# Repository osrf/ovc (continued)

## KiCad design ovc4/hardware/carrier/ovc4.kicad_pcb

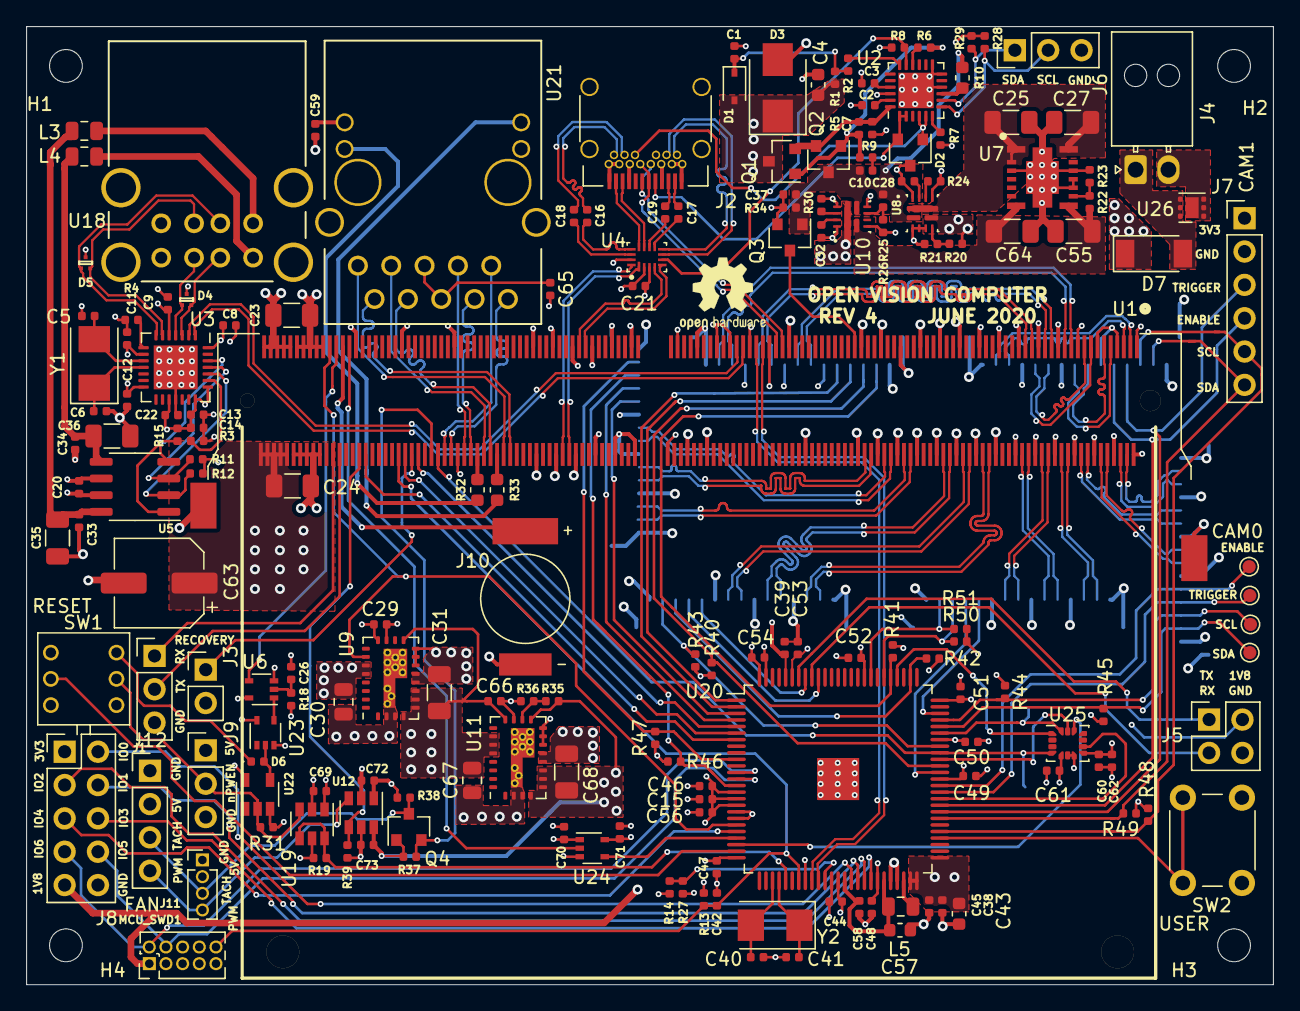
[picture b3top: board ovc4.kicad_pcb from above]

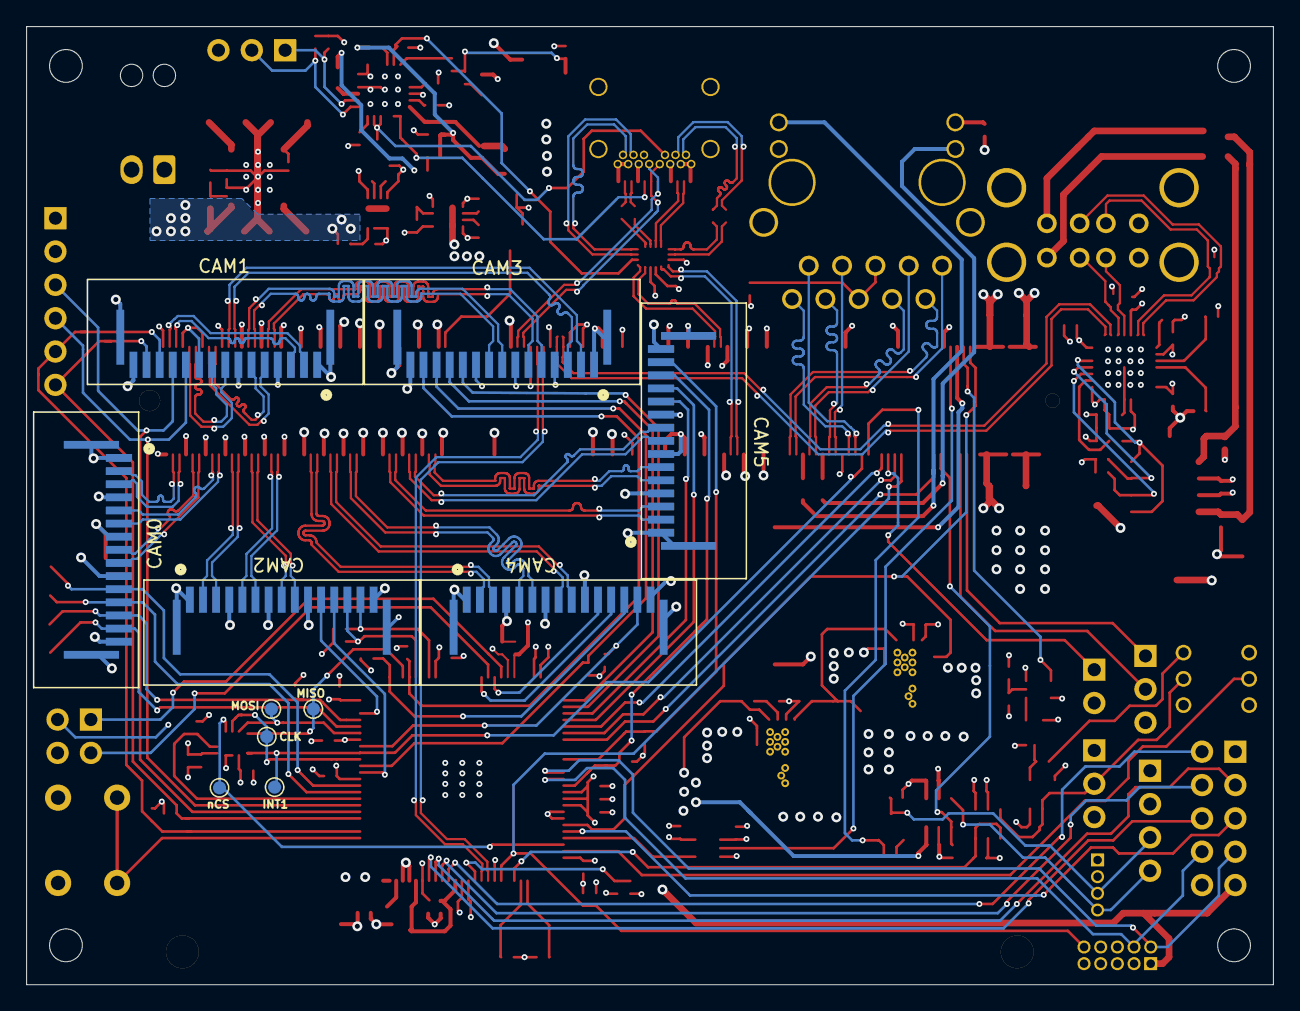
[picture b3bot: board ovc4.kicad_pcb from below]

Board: 6 copper layers, 95.0 x 73.0 mm, 194 parts (11 on the bottom side), 188 nets.

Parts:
C1, C2, C3, C7, C14, C22, C26, C29, C66: 1u; C_0402_1005Metric
C4: 4u7; C_0603_1608Metric
C5, C6, C40, C41: 18p; C_0402_1005Metric
C8: 10u; C_0402_1005Metric
C9, C10, C11, C12, C13, C15, C16, C17, C18, C19, C20, C21, C28, C32, C33, C34, C37, C38, C39, C42, C44, C46, C47, C48, C49, C50, C51, C52, C53, C54, C56, C58, C59, C60, C61, C65, C69, C70, C71, C72, C73: 100n; C_0402_1005Metric
C23, C24, C35, C36: 100u; C_1206_3216Metric
C25, C27: 10u; C_1206_3216Metric
C30, C67: 10u; C_0805_2012Metric
C31, C55, C64, C68: 47u; C_1206_3216Metric
C43, C57: 10u; C_0603_1608Metric
C45: 47p; C_0402_1005Metric
C62: 2u2; C_0402_1005Metric
C63: 470u; CP_Elec_6.3x7.7
CAM0, CAM1, CAM2, CAM3, CAM4, CAM5: PICAM; AMPHENOL_SFW15R
D1: SDMK0340L-7-F; D_SOD-323
D2: ESDA25W; SOT-23
D3: SMBJ22A; D_SMB
D4, D5: D_TVS_x2_AAC; TPD2EUSB30x
D6: D; D_0402_1005Metric
D7: PMEG3030EP,115; D_SOD-128
H1, H2, H3, H4: MountingHole; MountingHole_2.5mm
J1, J6, J9: Conn_01x03; PinHeader_1x03_P2.54mm_Vertical
J2: USB_C_Receptacle; USB_C_Receptacle_Wurth_632723300011
J3: Conn_01x02; PinHeader_1x02_P2.54mm_Vertical
J4: Conn_01x02; Molex_Nano-Fit_105313-xx02_1x02_P2.50mm_Horizontal
J5: ISP_UART; PinHeader_2x02_P2.54mm_Vertical
J7: Conn_01x06; PinHeader_1x06_P2.54mm_Vertical
J8: Conn_02x05_Odd_Even; PinHeader_2x05_P2.54mm_Vertical
J10: Conn_01x02; ELNA_DSK-3R3H224U-HL
J11: Conn_01x04; PinHeader_1x04_P1.27mm_Vertical
J12: Conn_01x04; PinHeader_1x04_P2.54mm_Vertical
L3, L4, L5: 4u7; L_0805_2012Metric
LOGO1: Logo_Open_Hardware_Large; OSHW-Logo2_7.3x6mm_SilkScreen
MCU_SWD1: Conn_ARM_JTAG_SWD_10; PinHeader_2x05_P1.27mm_Vertical
Q1, Q2: SI2369DS; SOT-23
Q3, Q4: 2N7002; SOT-23
R1: 470R; R_0402_1005Metric
R2: 1k; R_0402_1005Metric
R3, R5, R7, R8, R13, R15, R39: 100k; R_0402_1005Metric
R4: 649R; R_0402_1005Metric
R6, R24, R30: 22k; R_0402_1005Metric
R9: 100R; R_0402_1005Metric
R10: 1k; R_0603_1608Metric
R11, R12, R14, R18, R19, R22, R31, R37, R38: 10k; R_0402_1005Metric
R20, R25, R27: 20k; R_0402_1005Metric
R21, R26: 4k7; R_0402_1005Metric
R23, R28, R29, R40, R41, R42, R43, R44, R45, R46, R47, R48, R49, R50, R51: 2k4; R_0402_1005Metric
R32, R33: 110R; R_0603_1608Metric
R34: 1M; R_0402_1005Metric
R35: 340k; R_0402_1005Metric
R36: 162k; R_0402_1005Metric
SW1: SW_DPDT_x2; TL2230
SW2: SW_Push; SW_PUSH_6mm_H5mm
TP1, TP2, TP3, TP4, TP5, TP6, TP7, TP8, TP9: Testpoint; TestPoint_Pad_D1.0mm
U1: Jetson_Nano; TE_2309413-1
U2: STUSB4500; QFN-24-1EP_4x4mm_P0.5mm_EP2.7x2.7mm
U3: CY7C65642-28LTXC; QFN-28-1EP_5x5mm_P0.5mm_EP3.35x3.35mm
U4: HD3SS3202; TI_R_PUQFN_N16
U5: LM3526-L; SO-8_3.9x4.9mm_P1.27mm
U6: 74AHC1G08; SOT-353_SC-70-5
U7: TPSM53604; TI_B3QFN
U8, U10: TPS2121; Texas_VQFN-HR-12_2x2.5_Pitch0.5mm
U9, U11: EN5322QI; Converter_DCDC_Intel_QFN-24_4x6mm_P0.65mm_ThermalVias
U12, U19: SN74LVC1T45DBV; SOT-23-6
U18: USBA_DUAL; USBA_DUAL_HOR
U20: LPC55S69JBD100; QFP-100-1EP_3.21x3.21mm_14x14_Pitch0.5mm
U21: ARJ11C-MBSAS-A-BA-7MU2
U22: 74LVC1G34; SOT-23-5
U23: SN74LVC1G04; SOT-353_SC-70-5
U24: SN74AUP1T34DCK; SOT-353_SC-70-5
U25: ICM42688; LGA-14_3x2.5mm_P0.5mm_LayoutBorder3x4y
U26: TVS2200DRV; WSON-6-1EP_2x2mm_P0.65mm_EP1x1.6mm
Y1: 12MHz; Crystal_SMD_5032-2Pin_5.0x3.2mm
Y2: 16MHz; Crystal_SMD_5032-2Pin_5.0x3.2mm

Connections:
+1V8: C15.2, C38.2, C43.1, C45.2, C46.2, C47.2, C48.2, C49.2, C50.2, C51.2, C52.2, C53.2, C54.2, C56.2, C60.2, C61.2, C62.2, C68.1, C71.1, C73.1, J5.2, J8.9, MCU_SWD1.1 (VTref), Q4.1 (G), R13.2, R35.1, R37.1, R40.1, R41.1, R42.1, R43.1, R44.1, R45.1, R46.1, R47.1, R48.1, R49.1, R50.1, R51.1, U11.4 (VOUT), U11.5 (VOUT), U11.6 (VOUT), U11.7 (VOUT), U11.13 (VSENSE), U12.6 (VCCB), U20.15 (VDD), U20.16 (VDDA), U20.17 (VREFP), U20.25 (VDD), U20.44 (VDD), U20.49 (VBAT_DCDC), U20.50 (VBAT_DCDC), U20.51 (VBAT_PMU), U20.63 (VDD), U20.69 (VDD), U20.75 (VDD), U20.84 (VDD), U20.95 (VDD), U20.100 (VDD), U24.5 (VCCB), U25.5 (VDDIO), U25.8 (VDD)
+3V3: C8.2, C9.2, C11.2, C12.2, C13.2, C14.2, C21.2, C22.2, C31.1, C39.2, C44.2, C59.2, C66.1, C67.1, CAM0.15 (3V3), CAM1.15 (3V3), CAM2.15 (3V3), CAM3.15 (3V3), CAM4.15 (3V3), CAM5.15 (3V3), J7.1, J8.1, R8.1, R11.1, R12.1, R15.1, R28.1, R29.1, U2.22 (VSYS), U3.5 (VCC_A), U3.9 (VCC_A), U3.14 (VCC_A), U3.17 (nRESET), U3.21 (VCC_D), U3.22 (SELFPWR), U3.28 (VREG), U4.3 (VCC), U9.4 (VOUT), U9.5 (VOUT), U9.6 (VOUT), U9.7 (VOUT), U9.13 (VSENSE), U11.10 (VS2), U11.11 (VS1), U11.12 (VS0), U11.16 (AVIN), U11.18 (ENABLE), U11.19 (PVIN), U11.20 (PVIN), U20.38 (USB1_3V3), U20.96 (USB0_3V3), U21.12 (GRNYEL_A), U21.13 (GRN_A)
+5V: C20.2, C23.1, C24.1, C29.1, C30.1, C63.1, C69.1, C70.1, C72.1, J9.1, J11.2, J12.2, R14.1, R18.1, R38.1, U1.251 (VDD_IN), U1.252 (VDD_IN), U1.253 (VDD_IN), U1.254 (VDD_IN), U1.255 (VDD_IN), U1.256 (VDD_IN), U1.257 (VDD_IN), U1.258 (VDD_IN), U1.259 (VDD_IN), U1.260 (VDD_IN), U5.7 (IN), U6.5 (VCC), U9.16 (AVIN), U9.19 (PVIN), U9.20 (PVIN), U10.1 (OUT), U10.8 (OUT), U12.1 (VCCA), U19.1 (VCCA), U22.5 (VCC), U23.5 (VCC), U24.1 (VCCA)
/Interfaces/FAN_PWM: R39.2, U1.230 (GPIO14), U12.4 (B)
/Interfaces/FAN_PWM_5V: J11.4, J12.4, U12.3 (A)
/Interfaces/FAN_TACH: Q4.2 (S), R37.2, U1.208 (GPIO08)
/Interfaces/FAN_TACH_5V: J11.3, J12.3, Q4.3 (D), R38.2
/Interfaces/USB0_VBUS: Q3.3 (D), U1.87 (GPIO0)
/MCU/IMU_CLK: TP2.1, U20.66 (PIO0_28/WAKEUP), U25.13 (SCL/SCLK)
/MCU/IMU_CS: TP1.1, U20.23 (PIO0_31/ADC0_3), U25.12 (CS)
/MCU/IMU_FSYNC: U20.60 (PIO0_26), U25.9 (INT2/FSYNC/CLKIN)
/MCU/IMU_MISO: TP4.1, U20.79 (PIO0_25), U25.1 (SDO/AD0)
/MCU/IMU_MOSI: TP3.1, U20.70 (PIO0_24), U25.14 (SDA/SDIO/SDI)
/MCU/ISP_USART_RXD: J5.3, U20.92 (PIO0_29)
/MCU/ISP_USART_TXD: J5.1, U20.94 (PIO0_30)
/MCU/MCU_GPIO0: J8.2, U20.40 (PIO1_10)
/MCU/MCU_GPIO1: J8.4, U20.41 (PIO1_22)
/MCU/MCU_GPIO2: J8.3, U20.42 (PIO1_23)
/MCU/MCU_GPIO3/FC6: J8.6, U20.43 (PIO1_17)
/MCU/MCU_GPIO4/FC6: J8.5, U20.21 (PIO0_10/ADC0_1)
/MCU/MCU_GPIO_BUTTON: SW2.1, U20.54 (PIO0_0/ACMP0_A)
/MCU/SWDCLK/MCU_GPIO5/FC6: J8.8, MCU_SWD1.4 (SWDCLK/TCK), U20.13 (PIO0_11/ADC0_9)
/MCU/SWDIO/MCU_GPIO6/FC6: J8.7, MCU_SWD1.2 (SWDIO/TMS), U20.12 (PIO0_12/ADC0_10)
/Power/AUX_PWR: D7.2 (A), J4.1, U26.4 (IN), U26.5 (IN), U26.6 (IN)
/Power/BATT: J10.2, U1.235 (PMIC_BBAT)
/Power/CTRL_PWEN: U6.1, U23.4
/Power/MCU_nPWEN_5V: J9.2, R31.1, SW1.2 (B), U19.3 (A), U22.2
/Power/NX_nSHUTDOWN_REQ: U1.233 (nSHUTDOWN_REQ), U24.2 (A)
/Power/OV1: R25.2, R26.1, U10.5 (OV1)
/Power/POWER_EN: U1.237 (POWER_EN), U6.4
/Power/PR1: R20.2, R21.1, U8.6 (PR1)
/Power/VAUX: D7.1 (K), R20.1, U8.7 (IN1)
/Power/VREG_5V: C55.1, C64.1, R22.1, U7.7 (VOUT), U7.8 (VOUT), U10.2 (IN2)
/Power/VREG_IN: C25.1, C27.1, U7.1 (VIN), U7.2 (EN), U7.14 (VIN), U8.1 (OUT), U8.8 (OUT)
/Power/nFORCE_RECOVERY: J3.1, U1.214 (nFORCE_RECOVERY)
/Power/nPWEN_LATCH: D6.2 (A), U22.4, U23.2
/USB/1V2: C3.1, U2.21 (VREG_1V2)
/USB/2V7: C2.1, U2.23 (VREG_2V7)
/USB/ABSIDE: R8.2, U2.17 (A_B_SIDE), U4.6 (SEL)
/USB/CONN_CC1: D2.2 (K), J2.A5 (CC1), U2.1 (CC1DB), U2.2 (CC1)
/USB/CONN_CC2: D2.1 (K), J2.B5 (CC2), U2.4 (CC2), U2.5 (CC2DB)
/USB/CONN_RX1+: J2.B11 (RX1+), U4.8 (C1+)
/USB/CONN_RX1-: J2.B10 (RX1-), U4.7 (C1-)
/USB/CONN_RX2+: J2.A11 (RX2+), U4.12 (B1+)
/USB/CONN_RX2-: J2.A10 (RX2-), U4.11 (B1-)
/USB/CONN_TX1+: C17.2, J2.A2 (TX1+)
/USB/CONN_TX1-: C19.2, J2.A3 (TX1-)
/USB/CONN_TX2+: C16.2, J2.B2 (TX2+)
/USB/CONN_TX2-: C18.2, J2.B3 (TX2-)
/USB/CONN_VBUS: C4.1, D1.2 (A), D3.1 (A1), J2.A4 (VBUS), J2.A9 (VBUS), J2.B4 (VBUS), J2.B9 (VBUS), Q1.3 (D), R1.1
/USB/DISCH: R10.2, U2.9 (DISCH)
/USB/GATES: Q1.1 (G), Q2.1 (G), R5.2, R6.1, R9.2
/USB/HUB_nOVR0: R11.2, U3.25 (nOVR1), U5.3 (FLAGB)
/USB/HUB_nOVR1: R12.2, U3.24 (nOVR2), U5.2 (FLAGA)
/USB/HUB_nPWR: R15.2, U3.26 (nPWR/SDA), U5.1 (nENA), U5.4 (nENB)
/USB/RESET: R7.1, U2.6 (RESET)
/USB/T1+: C17.1, U4.9 (C0-)
/USB/T1-: C19.1, U4.10 (C0+)
/USB/T2+: C16.1, U4.13 (B0-)
/USB/T2-: C18.1, U4.14 (B0+)
/USB/USB0_D_N: J2.A7 (D-), J2.B7 (D-), U1.109 (USB0_D_N)
/USB/USB0_D_P: J2.A6 (D+), J2.B6 (D+), U1.111 (USB0_D_P)
/USB/USB2_D_N: U1.121 (USB2_D_N), U3.1 (D_N)
/USB/USB2_D_P: U1.123 (USB2_D_P), U3.2 (D_P)
/USB/USB2_USER0_D_N: D4.2 (A2), U3.3 (DD1_N), U18.2 (D-A)
/USB/USB2_USER0_D_P: D4.1 (A1), U3.4 (DD1_P), U18.3 (D+A)
/USB/USB2_USER1_D_N: D5.2 (A2), U3.6 (DD2_N), U18.7 (D+B)
/USB/USB2_USER1_D_P: D5.1 (A1), U3.7 (DD2_P), U18.6 (D-B)
/USB/USBSS_RX_N: U1.161 (USBSS_RX_N), U4.5 (A1-)
/USB/USBSS_RX_P: U1.163 (USBSS_RX_P), U4.4 (A1+)
/USB/USBSS_TX_N: U1.168 (USBSS_TX_P), U4.16 (A0+)
/USB/USBSS_TX_P: U1.166 (USBSS_TX_N), U4.1 (A0-)
/USB/VBUS_USER0: L4.2, U18.1 (VBUSA)
/USB/VBUS_USER1: L3.2, U18.5 (VBUSB)
/USB/VCC_USER0USB: C34.2, C36.2, L4.1, U5.5 (OUTB)
/USB/VCC_USER1USB: C33.2, C35.2, L3.1, U5.8 (OUTA)
CAM0_CLK+: CAM0.9 (CLK+), U1.12 (CSI0_CLK_P)
CAM0_CLK-: CAM0.8 (CLK-), U1.10 (CSI0_CLK_N)
CAM0_DAT0+: CAM0.3 (DAT0+), U1.6 (CSI0_D0_P)
CAM0_DAT0-: CAM0.2 (DAT0-), U1.4 (CSI0_D0_N)
CAM0_DAT1+: CAM0.6 (DAT1+), U1.18 (CSI0_D1_P)
CAM0_DAT1-: CAM0.5 (DAT1-), U1.16 (CSI0_D1_N)
CAM0_ENABLE: CAM0.11 (ENABLE), TP9.1, U20.62 (PIO1_3)
CAM0_SCL_1V8: CAM0.13 (SCL), R44.2, TP7.1, U20.72 (PIO0_14)
CAM0_SDA_1V8: CAM0.14 (SDA), R45.2, TP6.1, U20.71 (PIO0_13)
CAM0_TRIGGER: CAM0.12 (GPIO/NC), TP8.1, U20.61 (PIO1_2)
CAM1_CLK+: CAM1.9 (CLK+), U1.11 (CSI1_CLK_P)
CAM1_CLK-: CAM1.8 (CLK-), U1.9 (CSI1_CLK_N)
CAM1_DAT0+: CAM1.3 (DAT0+), U1.5 (CSI1_D0_P)
CAM1_DAT0-: CAM1.2 (DAT0-), U1.3 (CSI1_D0_N)
CAM1_DAT1+: CAM1.6 (DAT1+), U1.17 (CSI1_D1_P)
CAM1_DAT1-: CAM1.5 (DAT1-), U1.15 (CSI1_D1_N)
CAM1_ENABLE: CAM1.11 (ENABLE), J7.4, U20.59 (PIO1_1/WAKEUP)
CAM1_SCL_1V8: CAM1.13 (SCL), J7.5, R48.2, U20.55 (PIO0_9/ACMP0_B)
CAM1_SDA_1V8: CAM1.14 (SDA), J7.6, R49.2, U20.57 (PIO1_14/ACMP0_D)
CAM1_TRIGGER: CAM1.12 (GPIO/NC), J7.3, U20.58 (PIO1_19/ACMPVREF)
CAM2_CLK+: CAM2.9 (CLK+), U1.30 (CSI2_CLK_P)
CAM2_CLK-: CAM2.8 (CLK-), U1.28 (CSI2_CLK_N)
CAM2_DAT0+: CAM2.3 (DAT0+), U1.24 (CSI2_D0_P)
CAM2_DAT0-: CAM2.2 (DAT0-), U1.22 (CSI2_D0_N)
CAM2_DAT1+: CAM2.6 (DAT1+), U1.36 (CSI2_D1_P)
CAM2_DAT1-: CAM2.5 (DAT1-), U1.34 (CSI2_D1_N)
CAM2_ENABLE: CAM2.11 (ENABLE), U20.73 (PIO1_28)
CAM2_SCL_1V8: CAM2.13 (SCL), R50.2, U20.81 (PIO0_2/TRST)
CAM2_SDA_1V8: CAM2.14 (SDA), R51.2, U20.83 (PIO0_3/TCK)
CAM2_TRIGGER: CAM2.12 (GPIO/NC), U20.64 (PIO1_18/WAKEUP)
CAM3_CLK+: CAM3.9 (CLK+), U1.29 (CSI3_CLK_P)
CAM3_CLK-: CAM3.8 (CLK-), U1.27 (CSI3_CLK_N)
CAM3_DAT0+: CAM3.3 (DAT0+), U1.23 (CSI3_D0_P)
CAM3_DAT0-: CAM3.2 (DAT0-), U1.21 (CSI3_D0_N)
CAM3_DAT1+: CAM3.6 (DAT1+), U1.35 (CSI3_D1_P)
CAM3_DAT1-: CAM3.5 (DAT1-), U1.33 (CSI3_D1_N)
CAM3_ENABLE: CAM3.11 (ENABLE), U20.2 (PIO1_13)
CAM3_SCL_1V8: CAM3.13 (SCL), R40.2, U20.65 (PIO1_30/WAKEUP)
CAM3_SDA_1V8: CAM3.14 (SDA), R41.2, U20.80 (PIO1_29)
CAM3_TRIGGER: CAM3.12 (GPIO/NC), U20.1 (PIO1_4)
CAM4_CLK+: CAM4.9 (CLK+), U1.54 (CSI4_CLK_P)
CAM4_CLK-: CAM4.8 (CLK-), U1.52 (CSI4_CLK_N)
CAM4_DAT0+: CAM4.3 (DAT0+), U1.48 (CSI4_D0_P)
CAM4_DAT0-: CAM4.2 (DAT0-), U1.46 (CSI4_D0_N)
CAM4_DAT1+: CAM4.6 (DAT1+), U1.60 (CSI4_D1_P)
CAM4_DAT1-: CAM4.5 (DAT1-), U1.58 (CSI4_D1_N)
CAM4_ENABLE: CAM4.11 (ENABLE), U20.93 (PIO1_11)
CAM4_SCL_1V8: CAM4.13 (SCL), R42.2, U20.77 (PIO1_25)
CAM4_SDA_1V8: CAM4.14 (SDA), R43.2, U20.68 (PIO1_26)
CAM4_TRIGGER: CAM4.12 (GPIO/NC), U20.91 (PIO1_31)
CAM5_CLK+: CAM5.9 (CLK+), U1.78 (DSI_CLK_P)
CAM5_CLK-: CAM5.8 (CLK-), U1.76 (DSI_CLK_N)
CAM5_DAT0+: CAM5.3 (DAT0+), U1.72 (DSI_D0_P)
CAM5_DAT0-: CAM5.2 (DAT0-), U1.70 (DSI_D0_N)
CAM5_DAT1+: CAM5.6 (DAT1+), U1.84 (DSI_D1_P)
CAM5_DAT1-: CAM5.5 (DAT1-), U1.82 (DSI_D1_N)
CAM5_ENABLE: CAM5.11 (ENABLE), U20.3 (PIO1_24)
CAM5_SCL_1V8: CAM5.13 (SCL), R46.2, U20.14 (PIO0_16/ADC0_8)
CAM5_SDA_1V8: CAM5.14 (SDA), R47.2, U20.10 (PIO1_9/ADC0_12)
CAM5_TRIGGER: CAM5.12 (GPIO/NC), U20.4 (PIO1_20)
DEBUG_UART_RXD: J1.1, U1.238 (UART2_RXD)
DEBUG_UART_TXD: J1.2, U1.236 (UART2_TXD)
FRAME_TRIGGER: U1.212 (GPIO10), U20.5 (PIO1_6)
GBE_LED_ACT: R32.2, U1.194 (GBE_LED_ACT)
GBE_LED_LINK: R33.2, U1.188 (GBE_LED_LINK)
GBE_MDI0_N: U1.184 (GBE_MDI0_N), U21.2 (TRD0-)
GBE_MDI0_P: U1.186 (GBE_MDI0_P), U21.1 (TRD0+)
GBE_MDI1_N: U1.190 (GBE_MDI1_N), U21.4 (TRD1-)
GBE_MDI1_P: U1.192 (GBE_MDI1_P), U21.3 (TRD1+)
GBE_MDI2_N: U1.196 (GBE_MDI2_N), U21.8 (TRD2-)
GBE_MDI2_P: U1.198 (GBE_MDI2_P), U21.7 (TRD2+)
GBE_MDI3_N: U1.202 (GBE_MDI3_N), U21.10 (TRD3-)
GBE_MDI3_P: U1.204 (GBE_MDI3_P), U21.9 (TRD3+)
GND: C1.2, C2.2, C3.2, C4.2, C5.1, C6.2, C7.2, C8.1, C9.1, C11.1, C12.1, C13.1, C14.1, C15.1, C20.1, C21.1, C22.1, C23.2, C24.2, C25.2, C26.2, C27.2, C28.2, C29.2, C30.2, C31.2, C32.2, C33.1, C34.1, C35.1, C36.1, C37.2, C38.1, C39.1, C40.1, C41.1, C42.2, C43.2, C44.1, C45.1, C46.1, C47.1, C48.1, C49.1, C50.1, C51.1, C52.1, C53.1, C54.1, C55.2, C56.1, C57.2, C58.1, C59.1, C60.1, C61.1, C62.1, C63.2, C64.2, C65.2, C66.2, C67.2, C68.2, C69.2, C70.2, C71.2, C72.2, C73.2, CAM0.1 (GND), CAM0.4 (GND), CAM0.7 (GND), CAM0.10 (GND), CAM0.16 (PAD), CAM1.1 (GND), CAM1.4 (GND), CAM1.7 (GND), CAM1.10 (GND), CAM1.16 (PAD), CAM2.1 (GND), CAM2.4 (GND), CAM2.7 (GND), CAM2.10 (GND), CAM2.16 (PAD), CAM3.1 (GND), CAM3.4 (GND), CAM3.7 (GND), CAM3.10 (GND), CAM3.16 (PAD), CAM4.1 (GND), CAM4.4 (GND), CAM4.7 (GND), CAM4.10 (GND), CAM4.16 (PAD), CAM5.1 (GND), CAM5.4 (GND), CAM5.7 (GND), CAM5.10 (GND), CAM5.16 (PAD), D2.3 (A), D3.2 (A2), D4.3 (common), D5.3 (common), J1.3, J2.A1 (GND), J2.A12 (GND), J2.B1 (GND), J2.B12 (GND), J2.S1 (SHIELD), J3.2, J4.2, J5.4, J6.3, J7.2, J8.10, J9.3, J10.1, J11.1, J12.1, MCU_SWD1.3 (GND), MCU_SWD1.5 (GND), MCU_SWD1.9 (GNDDetect), Q3.2 (S), R3.2, R4.2, R7.2, R19.1, R21.2, R23.2, R24.2, R26.2, R27.2, R30.2, R31.2, R34.2, R36.2, R39.1, SW1.6 (C), SW2.2, U1.1 (GND), U1.2 (GND), U1.7 (GND), U1.8 (GND), U1.13 (GND), U1.14 (GND), U1.19 (GND), U1.20 (GND), U1.25 (GND), U1.26 (GND), U1.31 (GND), U1.32 (GND), U1.37 (GND), U1.38 (GND), U1.43 (GND), U1.44 (GND), U1.49 (GND), U1.50 (GND), U1.55 (GND), U1.56 (GND), U1.61 (GND), U1.62 (GND), U1.67 (GND), U1.68 (GND), U1.73 (GND), U1.74 (GND), U1.79 (GND), U1.80 (GND), U1.85 (GND), U1.86 (GND), U1.102 (GND), U1.107 (GND), U1.113 (GND), U1.119 (GND), U1.125 (GND), U1.129 (GND), U1.132 (GND), U1.135 (GND), U1.138 (GND), U1.141 (GND), U1.144 (GND), U1.146 (GND), U1.147 (GND), U1.152 (GND), U1.153 (GND), U1.158 (GND), U1.159 (GND), U1.164 (GND), U1.165 (GND), U1.170 (GND), U1.171 (GND), U1.176 (GND), U1.177 (GND), U1.200 (GND), U1.201 (GND), U1.217 (GND), U1.231 (GND), U1.241 (GND), U1.242 (GND), U1.243 (GND), U1.244 (GND), U1.245 (GND), U1.246 (GND), U1.247 (GND), U1.248 (GND), U1.249 (GND), U1.250 (GND), U1.261 (MNT), U1.262 (MNT), U2.10 (GND), U2.12 (ADDR0), U2.13 (ADDR1), U2.25 (PAD), U3.18 (TEST/SCL), U3.29 (GND), U4.2 (GND), U4.15 (~OE), U5.6 (GND), U6.3 (GND), U7.3 (NC/GND), U7.10 (NC/GND), U7.11 (NC/GND), U7.12 (AGND), U7.15 (PGND), U8.3 (CP2), U8.4 (OV2), U8.5 (OV1), U8.9 (ST), U8.12 (GND), U9.2 (PGND), U9.3 (PGND), U9.8 (PGND), U9.9 (PGND), U9.10 (VS2), U9.11 (VS1), U9.12 (VS0), U9.15 (AGND), U9.25 (PGND), U10.3 (CP2), U10.6 (PR1), U10.9 (ST), U10.12 (GND), U11.2 (PGND), U11.3 (PGND), U11.8 (PGND), U11.9 (PGND), U11.15 (AGND), U11.25 (PGND), U12.2 (GND), U12.5 (DIR), U18.4 (GNDA), U18.8 (GNDB), U18.9 (Shield), U19.2 (GND), U19.5 (DIR), U20.18 (VREFN), U20.19 (VSSA), U20.33 (USB1_VSS), U20.37 (USB1_VSS), U20.46 (VSS_DCDC), U20.47 (VSS_DCDC), U20.99 (USB0_VSS), U20.101 (VSS), U21.MNT, U21.SHLD, U22.3 (GND), U23.3 (GND), U24.3 (GND), U25.6 (GND), U25.7 (RESV/GND), U26.1 (GND), U26.2 (GND), U26.3 (GND), U26.7 (GND)
IMU_INT1: TP5.1, U1.206 (GPIO07), U20.67 (PIO1_12), U25.4 (INT1/INT)
MCU_USB1_D_N: U1.115 (USB1_D_N), U20.35 (USB1_DM)
MCU_USB1_D_P: U1.117 (USB1_D_P), U20.34 (USB1_DP)
MCU_nPWEN: R19.2, U19.4 (B), U19.6 (VCCB), U20.30 (PIO1_21)
NX_MCU_BOOT: U1.228 (GPIO13), U20.7 (PIO0_1)
NX_MCU_GPIO: U1.216 (GPIO11), U20.6 (PIO0_7)
NX_MCU_nRST: C42.1, MCU_SWD1.10 (~RESET~), R13.1, U1.218 (GPIO12), U20.32 (RESETN)
unnamed: C1.1, D1.1 (K), R1.2, R2.1
unnamed: C5.2, U3.10 (XIN), Y1.2
unnamed: C6.1, U3.11 (XOUT), Y1.1
unnamed: C7.1, Q1.2 (S), Q2.2 (S), R5.1, U2.24 (VDD)
unnamed: C10.2, R9.1
unnamed: C26.1, R18.2, U6.2
unnamed: C28.1, U8.11 (SS)
unnamed: C32.1, U10.11 (SS)
unnamed: C40.2, U20.28 (XTAL32M_N), Y2.2
unnamed: C41.2, U20.29 (XTAL32M_P), Y2.1
unnamed: C57.1, C58.2, L5.2, U20.39 (VDD_PMU), U20.45 (FB)
unnamed: C65.1, U21.5 (CT), U21.6 (CT)
unnamed: D6.1 (K), SW1.1 (A)
unnamed: L5.1, U20.48 (LX)
unnamed: R2.2, U2.18 (VBUS_VS_DISCH)
unnamed: R3.1, U3.23 (GANG)
unnamed: R4.1, U3.8 (RREF)
unnamed: R6.2, U2.16 (VBUS_EN_SINK)
unnamed: R14.2, R27.1, U20.36 (USB1_VBUS)
unnamed: R22.2, R23.1, U7.9 (FB)
unnamed: R24.1, U8.10 (ILIM)
unnamed: R30.1, U10.10 (ILIM)
unnamed: R32.1, U21.11 (GRNYEL_C)
unnamed: R33.1, U21.14 (GRN_C)
unnamed: R35.2, R36.1, U11.14 (VFB)
RST_BUTTON: SW1.5 (B), U20.24 (PIO1_8/ADC0_4)
USB_SCL: J6.2, R28.2, U2.7 (SCL)
USB_SDA: J6.1, R29.2, U2.8 (SDA)
VBUS: C10.1, C37.1, Q2.3 (D), Q3.1 (G), R10.1, R25.1, R34.1, U8.2 (IN2), U10.7 (IN1)
nSHUTDOWN_REQ: U20.22 (PIO0_15/ADC0_2), U24.4 (B)
nSYS_RESET: U1.239 (nSYS_RESET), U9.18 (ENABLE), U20.20 (PIO0_23)

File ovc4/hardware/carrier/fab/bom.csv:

Component,Quantity Per PCB,References,Value,Footprint,MFN,MPN,D1N,D1PN,voltage
1,41,C9 C10 C11 C12 C13 C15 C16 C17 C18 C19 C20 C21 C28 C32 C33 C34 C37 C38 C39 C42 C44 C46 C47 C48 C49 C50 C51 C52 C53 C54 C56 C58 C59 C60 C61 C65 C69 C70 C71 C72 C73,100n,C_0402_1005Metric,Samsung,CL05F104ZO5NNNC,Digikey,1276-1004-1-ND,
2,4,C23 C24 C35 C36,100u,C_1206_3216Metric,TDK,C3216X5R1A107M160AC,Digikey,445-6007-1-ND,
3,2,C25 C27,10u,C_1206_3216Metric,KEMET,C1206C106M3PACTU,Digikey,399-8153-1-ND,
4,2,C30 C67,10u,C_0805_2012Metric,Kemet,C0805C106K8PACTU,Digikey,399-4925-1-ND,
5,2,C43 C57,10u,C_0603_1608Metric,Murata,GRM188R61A106KE69J,Digikey,490-14372-1-ND,
6,1,C8,10u,C_0402_1005Metric,Murata,GRM155C80J106ME11J,Digikey,490-18210-1-ND,
7,4,C5 C6 C40 C41,18p,C_0402_1005Metric,Yageo,CC0402JRNPO9BN180,Digikey,311-1415-1-ND,
8,9,C1 C2 C3 C7 C14 C22 C26 C29 C66,1u,C_0402_1005Metric,Samsung,CL05A105KA5NQNC,Digikey,1276-1445-1-ND,
9,1,C62,2u2,C_0402_1005Metric,Murata,GRM155R61A225KE95D,Digikey,490-10451-1-ND,
10,1,C63,470u,CP_Elec_6.3x7.7,Panasonic,EEE-FTJ471XAP,Digikey,P15096CT-ND,
11,1,C45,47p,C_0402_1005Metric,Kemet,C0402C470K5GACTU,Digikey,399-7796-1-ND,
12,4,C31 C55 C64 C68,47u,C_1206_3216Metric,Murata,GRM31CR61A476KE15L,Digikey,490-9673-1-ND,
13,1,C4,4u7,C_0603_1608Metric,Samsung,CL10A475KA8NQNC,Digikey,1276-1900-1-ND,25V
14,6,CAM0 CAM1 CAM2 CAM3 CAM4 CAM5,PICAM,AMPHENOL_SFW15R,Amphenol,SFW15R-1STE1LF,Digikey,609-1905-1-ND,
15,1,D6,D,D_0402_1005Metric,Comchip,CDBQR0130L,Digikey,641-1271-1-ND,
16,2,D4 D5,D_TVS_x2_AAC,TPD2EUSB30x,TI,TPD2EUSB30DRTR,Digikey,296-25509-1-ND,
17,1,D2,ESDA25W,SOT-23,ST,ESDA25W,Digikey,497-6689-1-ND,
18,1,D7,"PMEG3030EP,115",D_SOD-128,Nexperia,"PMEG3030EP,115",Digikey,1727-5324-1-ND,
19,1,D1,SDMK0340L-7-F,D_SOD-323,Diodes Inc,SDMK0340L-7-F,Digikey,SDMK0340L-FDICT-ND,
20,1,D3,SMBJ22A,D_SMB,Bourns,SMBJ22A,Digikey,SMBJ22ABCT-ND,
21,1,J10,Conn_01x02,ELNA_DSK-3R3H224U-HL,Elna,DSK-3R3H224U-HL,Digikey,604-1020-1-ND,
22,1,J3,Conn_01x02,PinHeader_1x02_P2.54mm_Vertical,Harwin,952-2262-ND,Digikey,952-2262-ND,
23,1,J4,Conn_01x02,Molex_Nano-Fit_105313-xx02_1x02_P2.50mm_Horizontal,Molex,1053131302,Digikey,WM15141-ND,
24,3,J1 J6 J9,Conn_01x03,PinHeader_1x03_P2.54mm_Vertical,Wurth,CONN HEADER VERT 3POS 2.54MM,Digikey,732-5316-ND,
25,1,J11,Conn_01x04,PinHeader_1x04_P1.27mm_Vertical,Adam Tech,HPH1-B-04-UA,Digikey,2057-HPH1-B-04-UA-ND,
26,1,J12,Conn_01x04,PinHeader_1x04_P2.54mm_Vertical,Wurth,61300411121,Digikey,732-5317-ND,
27,1,J7,Conn_01x06,PinHeader_1x06_P2.54mm_Vertical,Amphenol,68000-406HLF,Digikey,609-3263-ND,
28,1,J8,Conn_02x05_Odd_Even,PinHeader_2x05_P2.54mm_Vertical,Sullins,PPTC052LFBN-RC,Digikey,S6105-ND,
29,1,J5,ISP_UART,PinHeader_2x02_P2.54mm_Vertical,Harwin,M20-9760246,Digikey,952-1772-ND,
30,1,J2,USB_C_Receptacle,USB_C_Receptacle_Wurth_632723300011,Wurth,632723300011,Digikey,732-9618-1-ND,
31,3,L3 L4 L5,4u7,L_0805_2012Metric,Murata,LQM2MPN4R7MG0L,Digikey,490-12073-1-ND,
32,1,LOGO1,Logo_Open_Hardware_Large,OSHW-Logo2_7.3x6mm_SilkScreen,,,,,
33,1,MCU_SWD1,Conn_ARM_JTAG_SWD_10,PinHeader_2x05_P1.27mm_Vertical,Amphenol,20021111-00010T4LF,Digikey,609-3712-ND,
34,2,Q3 Q4,2N7002,SOT-23,Nexperia,"2N7002,215",Digikey,1727-2764-1-ND,
35,2,Q1 Q2,SI2369DS,SOT-23,Vishay,SI2369DS-T1-GE3,Digikey,SI2369DS-T1-GE3CT-ND,
36,1,R9,100R,R_0402_1005Metric,Panasonic,ERA-2AED101X,Digikey,P100DECT-ND,
37,7,R3 R5 R7 R8 R13 R15 R39,100k,R_0402_1005Metric,Panasonic,ERA-2AED104X,Digikey,P100KDECT-ND,
38,9,R11 R12 R14 R18 R19 R22 R31 R37 R38,10k,R_0402_1005Metric,Panasonic,ERA-2AED103X,Digikey,P10KDECT-ND,
39,2,R32 R33,110R,R_0603_1608Metric,Panasonic,ERA-3AEB111V,Digikey,P110DBCT-ND,
40,1,R36,162k,R_0402_1005Metric,Panasonic,ERJ-2RKF1623X,Digikey,P162KLCT-ND,
41,1,R34,1M,R_0402_1005Metric,Yageo,RC0402FR-071ML,Digikey,311-1.00MLRCT-ND,
42,1,R10,1k,R_0603_1608Metric,Rohm,ESR03EZPJ102,Digikey,RHM1.0KDCT-ND,
43,1,R2,1k,R_0402_1005Metric,Panasonic,ERJ-2RKF1001X,Digikey,P1.00KLCT-ND,
44,3,R20 R25 R27,20k,R_0402_1005Metric,Panasonic,ERA-2AED203X,Digikey,P20KDECT-ND,
45,3,R6 R24 R30,22k,R_0402_1005Metric,Panasonic,ERJ-2RKF2202X,Digikey,P22.0KLCT-ND,
46,15,R23 R28 R29 R40 R41 R42 R43 R44 R45 R46 R47 R48 R49 R50 R51,2k4,R_0402_1005Metric,Panasonic,ERA-2AED242X,Digikey,P2.4KDECT-ND,
47,1,R35,340k,R_0402_1005Metric,Panasonic,ERJ-2RKF3403X,Digikey,P340KLCT-ND,
48,1,R1,470R,R_0402_1005Metric,Panasonic,ERJ-2RKF4700X,Digikey,P470LCT-ND,
49,2,R21 R26,4k7,R_0402_1005Metric,Panasonic,ERJ-2RKF4701X,Digikey,P4.70KLCT-ND,
50,1,R4,649R,R_0402_1005Metric,Panasonic,ERA-2AEB6490X,Digikey,P649DCCT-ND,
51,1,SW1,SW_DPDT_x2,TL2230,E-Switch,TL2230OAF140,Digikey,EG6032-ND,
52,1,SW2,SW_Push,SW_PUSH_6mm_H5mm,TE Connectivity,1825910-7,Digikey,450-1804-ND,
53,1,U6,74AHC1G08,SOT-353_SC-70-5,TI,SN74AHC1G08DCKR,Digikey,296-8743-1-ND,
54,1,U22,74LVC1G34,SOT-23-5,TI,SN74LVC1G34DBVR,Digikey,296-17893-1-ND,
55,1,U21,ARJ11C-MBSAS-A-BA-7MU2,ARJ11C-MBSAS-A-BA-7MU2,Abracon,ARJ11C-MBSAS-A-BA-7MU2,Digikey,ARJ11C-MBSAS-A-BA-7MU2-ND,
56,1,U3,CY7C65642-28LTXC,QFN-28-1EP_5x5mm_P0.5mm_EP3.35x3.35mm,Cypress,CY7C65642-28LTXC,Digikey,428-3149-ND,
57,2,U9 U11,EN5322QI,Converter_DCDC_Intel_QFN-24_4x6mm_P0.65mm_ThermalVias,Intel,EN5322QI,Digikey,544-2849-1-ND,
58,1,U4,HD3SS3202,TI_R_PUQFN_N16,TI,HD3SS3202IRSVT,Digikey,296-52295-1-ND,
59,1,U25,ICM42688,LGA-14_3x2.5mm_P0.5mm_LayoutBorder3x4y,TDK Invensense,ICM-42688-P,Digikey,1428-ICM-42688-PCT-ND,
60,1,U1,Jetson_Nano,TE_2309413-1,TE Connectivity,2309413-1,Digikey,A126764CT-ND,
61,1,U5,LM3526-L,SO-8_3.9x4.9mm_P1.27mm,TI,LM3526MX-L/NOPB,Digikey,LM3526MX-L/NOPBCT-ND,
62,1,U20,LPC55S66JBD100,QFP-100-1EP_3.21x3.21mm_14x14_Pitch0.5mm,NXP,LPC55S69JBD100K,Digikey,568-15313-ND,
63,1,U24,SN74AUP1T34DCK,SOT-353_SC-70-5,TI,SN74AUP1T34DCKR,Digikey,296-34900-1-ND,
64,1,U23,SN74LVC1G04,SOT-353_SC-70-5,TI,SN74LVC1G04DCKR,Digikey,296-11600-1-ND,
65,2,U12 U19,SN74LVC1T45DBV,SOT-23-6,TI,SN74LVC1T45DBVR,Digikey,296-16843-1-ND,
66,1,U2,STUSB4500,QFN-24-1EP_4x4mm_P0.5mm_EP2.7x2.7mm,ST,STUSB4500LQTR,Digikey,497-STUSB4500LQCT-ND,
67,2,U8 U10,TPS2121,Texas_VQFN-HR-12_2x2.5_Pitch0.5mm,TI,TPS2121RUXR,Digikey,296-53410-1-ND,
68,1,U7,TPSM53604,TI_B3QFN,TI,TPSM53604RDAR,Digikey,296-TPSM53604RDARCT-ND,
69,1,U26,TVS2200DRV,WSON-6-1EP_2x2mm_P0.65mm_EP1x1.6mm,TI,TVS2200DRVR,Mouser,595-TVS2200DRVR,
70,1,U18,USBA_DUAL,USBA_DUAL_HOR,Amphenol,72309-8034BLF,Digikey,609-1040-ND,
71,1,Y1,12MHz,Crystal_SMD_5032-2Pin_5.0x3.2mm,Kyocera,CX5032GB12000H0HPQZ1,Digikey,1253-1375-1-ND,
72,1,Y2,16MHz,Crystal_SMD_5032-2Pin_5.0x3.2mm,Kyocera,CX5032GB16000H0PESZZ,Digikey,478-4362-1-ND,





Component Groups:,72
Component Count:,181
Fitted Components:,181
Number of PCBs:,1
Total components:,181
Schematic Version:,
Schematic Date:,
PCB Variant:,['default']
BoM Date:,Mon Jun 22 18:16:15 2020
Schematic Source:,ovc4.kicad_sch
KiCad Version:,Eeschema 5.99.0-unknown-ad69e44~101~ubuntu18.04.1
